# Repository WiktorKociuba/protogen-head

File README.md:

# Protogen head
 <br>
It is a wearable protogen fursuit head that you can make at home! Just follow the readme bellow :3 I made it because I wanted to make a fursuit for a long time and I wanted to challenge my hardware skills as well as learn more about blender.
## Hardware
The PCB for this protogen head contains ESP32-S3-WROOM-1 and is powered by two USB-C ports/one USB-C port and XT-30 connector. You can connect to it:
- Two serialy connected HUB75 LED matrixes
- Two WS2812B LED strips (or any addresable LEDs)
- Two small fans
- One speaker
- One capacitive button <br>

It also has 10 GPIO pins exposed as well as two of each voltage pins. The +5VD net is used to power only LED Matrixes and the +5V powers the rest. ESP32 works on 3V3, so I had to use a LDO to power it. There are also two 74AHCT245PW used to change the logic voltage from 3V3 to 5V, so it can communicate with the peripherals that require 5V. The production files can be found in hardware/protogenHead/jlcpcb/production_files . <br>
 <br>
<br>
<br>
<br>

## 3D Model
You need at least 1700g of filament to print it. I recommend using PETG or something stronger, avoid PLA because it might not be strong enough. This protogen features two pairs of ears with a pair of side panels. It can also accomodate two Waveshare 20117 screens, PCB, two fans and you can additionally make a capacitive touch sensor to detect boops. Just connect a piece of for example aluminum foil via a wire to the designated PCB pin. Remember to calibrate the threshold value by checking how it changes when touched. Everything is mounted using M3 screws, you additionally need heat inserts for the ears.
 <br>

## Software
The source code is mainly in file software/src/main.cpp It has comments, so I will only describe here the functionality. In the future I want to add the ability to control the board over WiFi.
### LED Matrix control
The software uses ESP32-HUB75-MatrixPanel-I2S-DMA library. The pins are setup for the provided PCB so if you want to use your own, just modify it. It comes preloaded with one animation, you have to convert the bitmaps to header files that contain the pixel values. See the example files in software/src on how it looks like. Remember that the arrays have to be the size of your LED number.
### Additional LED control
You can connect two additional programmable LED strips/rings that share the same control pin. Then you just have to change the color to whatever you like in setLEDColor.
### Boop detection
You can add a capacitive sensor to the touch pin. You just have to test what values it gives back and set the threshold accordingly. I use it to play a sound using the FIT0449 speaker. Just provide a SoundData.h with the values of sound exported from Audacity or simmilar program. You can check out the example in software/src.
## How to build (will add more details after I build it)
1) Order the PCB using the gerber files provided in hardware/productionFiles
2) Order all components according to the BoM below
3) Print all the parts provided in 3D Models/print
4) Assemble the PCB and upload software using the opposite port to the ESP32
5) Vacuum form the visor (look at the tutorial provided in section vacuum forming)
6) Glue the magnets to the visor and to the bottom jaw.
7) Fur the base as you wish
8) Screw everything together with M3 screws, remember to embed heat inserts into the ears
9) Attach the visor and power everything with two USB-C cables connected to a powerbank or one USB-C cable on the port opposite to the ESP-32 and one battery connected to the XT30 connector.
### Vacuum forming
In order to vacuum form the visor, check the blender file to see how the vacuum forming rig looks like. Basically you have to use two plywood sheets for top and bottom, the top one should be perforated. Make a box with walls from square timber and connect everything with wood screws. Remember to seal everything with for example caulk or other sealant. You also have to make a hole for your vacuum tube and seal eat. You can also add rails to aid you with alligning the frame, just connect it to the box with for example corner braces. After that make the fram from square timber that will fit the PETG sheet, attach it together with wood screws so that it clamps the PETG sheet. You should also use some sandpaper or something that will create a lot of friction between the petg sheet and the frame, so it doesn't slip out. After that heat up the PETG sheet in oven until it sags, turn on the vacuum and then quickly press the PETG sheet onto the mold. Hold it there for few seconds and then it should be ready to go. Just cut it to shape and then dye it with iDye Poly or something simillar.

## BoM
### PCB
#### PCB Manufacturing

| Component | Qty | Price per item | Price |
| --------- | --- | -------------- | ----- |
| PCB (JLCPCB) | 10 | $0.5 | $5 |
| Stencil (JLCPCB) | 1 | $2.5 | $2.5 |
| Total | | | $7.5 |

#### PCB Components
| Designator | Component | Qty | Price Per Unit | Price |
| ---------- | --------- | --- | -------------- | ----- |
| C10 | [GRM219R61C226ME15L](https://www.tme.eu/pl/details/grm219r61c226me15l/) | 2 | 1.507 PLN | 3.01 PLN |
| C9, C11, C12 | [CL21A106KPFNNNG](https://www.tme.eu/pl/details/cl21a106kpfnnng/) | 10 | 0.333 PLN | 3.33 PLN |
| J1, J2 | [DG301-5.0-2P12](https://www.tme.eu/pl/details/dg301-5.0-2p12/) | 2 | 0.88 PLN | 1.76 PLN |
| C3 | [GRM188R60J106KE47D](https://www.tme.eu/pl/details/grm188r60j106ke47d/) | 10 | 0.145 PLN | 1.45 PLN |
| J8, J9 | [B2B-XH-A](https://www.tme.eu/pl/details/b2b-xh-a/) | 2 | 0.365 PLN | 0.73 PLN |
| C4, C6, C7, C8 | [CL10B104JB8NNNC](https://www.tme.eu/pl/details/cl10b104jb8nnnc/) | 10 | 0.248 PLN | 2.48 PLN |
| R4, R5 | [ERJ3EKF27R0V](https://www.tme.eu/pl/details/erj3ekf27r0v/) | 10 | 0.113 PLN | 1.13 PLN |
| R6, R7, R8, R9 | [ERJ3EKF5101V](https://www.tme.eu/pl/details/erj3ekf5101v/) | 10 | 0.079 PLN | 0.79 PLN |
| J11 | [ZL202-8G](https://www.tme.eu/pl/details/zl202-8g/) | 10 | 0.452 PLN | 4.52 PLN |
| U1 | [T821-1-16-S1](https://www.tme.eu/pl/details/t821-1-16-s1/) | 2 | 4.138 PLN | 8.28 PLN |
| J14 | [67997-410HLF](https://www.tme.eu/pl/details/67997-410hlf/) | 1 | 1.1 PLN | 1.1 PLN |
| R1, R2, R3 | [ERJ3EKF1002V](https://www.tme.eu/pl/details/erj3ekf1002v/) | 10 | 0.036 PLN | 0.36 PLN | 
| J10 | [XT30U-F](https://www.tme.eu/pl/details/xt30u-f/) | 1 | 4.45 PLN | 4.45 PLN |
| J12 | [DS1002-01-1X08V13](https://www.tme.eu/pl/details/ds1002-01-1x08v13/) | 5 | 1.349 PLN | 6.75 PLN |
| U2 | [ESP32S3-WRM1-16R8](https://www.tme.eu/pl/details/esp32s3-wrm1-16r8/) | 1 | 31.48 PLN | 31.48 PLN |
| J4, J5, J6 | [B3B-XH-A](https://www.tme.eu/pl/details/b3b-xh-a/) | 3 | 0.505 PLN | 1.52 PLN |
| U5, U6 | [74AHCT245PW.118](https://www.tme.eu/pl/details/74ahct245pw.118/) | 4 | 1.606 PLN | 6.43 PLN |
| J3, J7 | [USB4105-GF-A](https://www.tme.eu/pl/details/usb4105-gf-a/) | 3 | 3.535 PLN | 10.61 PLN |
| U3 | [AP2112K-3.3TRG1](https://www.tme.eu/pl/details/ap2112k-3.3trg1/) | 2 | 1.173 PLN | 2.35 PLN |
| C1, C2, C5 | [CC0603KRX7R8BB105](https://www.tme.eu/pl/details/cc0603krx7r8bb105/) | 10 | 0.411 PLN | 4.11 PLN |
| SW3, SW4 | [KMR221GLFS](https://www.tme.eu/pl/details/kmr221glfs/) | 3 | 2.401 PLN | 7.20 PLN |
| Pin cover | [NDR-08](https://www.tme.eu/pl/details/ndr-08/) | 10 | 0.574 PLN | 5.74 PLN |
| Pin cover | [NSR-02](https://www.tme.eu/pl/details/nsr-02/) | 20 | 0.24 PLN | 4.79 PLN |
| Total | | | | 114.35 PLN (~$28.12) |

### Other hardware 
| Component | Qty | Price per item | Price |
| --------- | --- | -------------- | ----- |
| [Waveshare 20117](https://kamami.pl/matrycowe/587574-rgb-matrix-p3-64x32-wyswietlacz-matrycowy-led-rgb-64x32-5906623465668.html) | 2 | 125.50 PLN | 251 PLN |
| [FIT0449](https://botland.com.pl/gravity-moduly-dzwiekowe/5501-dfrobot-gravity-glosnik-z-interfejsem-cyfrowym-6959420909575.html) | 1 | 26.90 PLN | 26.90 PLN
| [WS2812B](https://nettigo.pl/products/tasma-led-rgb-ws2812b-5v-bialy-podklad-60-m-ip67-wodoodporna) | 1 | 31 PLN | 31 PLN |
| [Sunon 1197317](https://kamami.pl/wentylatory/1197317-sunon-ee40100s2-1000u-999-5902186301221.html) | 2 | 10.20 PLN | 20.40 PLN |
| Total | | | 316.96 PLN (~$77.97)

### Vacuum forming
| Component | Qty | Price per item | Price |
| --------- | --- | -------------- | ----- |
| [50x50cm plywood](https://www.castorama.pl/departments/sklejka-brzozowa-wodoodporna-fosztt-6-mm-50-x-50-cm-1-szt/5908110070805_CAPL.prd) | 2 | 25 PLN | 50 PLN |
| [Square timber 19x60x1000mm](https://www.castorama.pl/kantowka-strugana-drewniana-floorpol-19-x-60-x-1000-mm/5907508714062_CAPL.prd) | 2 | 13.98 PLN | 27.96 PLN |
| [Square timber 10x40x1000mm](https://www.castorama.pl/kantowka-strugana-ostre-krawedzie-sosna-10x40x1000-mm/5063022667830_CAPL.prd) | 4 | 10.88 PLN | 43.52 PLN|
| [Square timber 10x10x1000mm](https://www.castorama.pl/kantowka-strugana-ostre-krawedzie-sosna-10x10x1000-mm/5063022667250_CAPL.prd) | 1 | 6.58 PLN | 6.58 PLN |
| [Corner brace](https://www.castorama.pl/katownik-stalowy-do-laczenia-elementow-z-przetloczeniem-25-x-25-x-15-mm-ocynk-bialy/5907484582167_CAPL.prd) | 4 | 2.98 PLN | 11.92 PLN |
| [Wood screw 6x100mm 10pcs](https://www.castorama.pl/wkrety-torx-diall-do-drewna-twardego-6-x-100-mm-10-szt-/5906675097350_CAPL.prd) | 1 | 13.98 PLN | 13.98 PLN |
| [Caulk](https://www.castorama.pl/silikon-uniwersalny-300-ml-bezbarwny/5059340043647_CAPL.prd) | 1 | 11 PLN | 11 PLN |
| [PETG Sheet 50x50cm 3mm](https://fabermedia.pl/plyty-z-tworzyw-sztucznych/plyty-pet/plyta-pet-bezbarwna-pet-g-3mm#/grubo%C5%9B%C4%87-3mm) | 2 | 52.54 PLN | 105.08 PLN |
| [iDye Poly Black](https://allegro.pl/produkt/jacquard-idye-poly-0-49oz-black-czarny-barwnik-do-tkanin-syntetycznych-a346e01e-34aa-4d9d-9f90-61f1dbddb3e5?offerId=19117603692&utm_source=google&utm_medium=product-carousel&utm_campaign=product-listing&utm_content=%2Flisting%3Fstring%3Didye%2520poly) | 1 | 35.68 PLN | 35.68 PLN | 
| Total | | | 305.72 PLN (~$74.83) |

### Other
| Component | Qty | Price per item | Price |
| --------- | --- | -------------- | ----- |
| [Screws M3 x 10mm 20pcs](https://www.castorama.pl/sruby-metryczne-z-lbem-cylindrycznym-ocynkowane-m3-x-10-mm-20-szt-/4001221784546_CAPL.prd) | 1 | 8.48 PLN | 8.48 PLN |
| [Screws M3 x 20mm 20pcs](https://www.castorama.pl/sruby-metryczne-z-lbem-cylindrycznym-ocynkowane-m3-x-20-mm-20-szt-/4001221784317_CAPL.prd) | 1 | 8.18 PLN | 8.18 PLN |
| [M3 Heat-set inserts](https://www.tme.eu/pl/details/b3_bn1045/wkladki-gwintowane/bossard/1386204/) | 10 | 0.511 PLN | 5.11 PLN |
| [Creality CR-PETG black](https://botland.com.pl/filamenty-petg/23007-filament-creality-cr-petg-175mm-1kg-black-6971636405344.html) | 2 | 49 PLN | 98 PLN |
| [Black fur](https://efutro.com.pl/product-pol-372-Fox-PREMIUM-365-czarny-Black-Frost-sztuczne-futro-niezwykle-puszyste-z-wlosem-o-dlugosci-do-60-mm.html) | 1 lm | 170.10 PLN | 170.10 PLN |
| [Purple fur](https://efutro.com.pl/product-pol-608-Fox-Fioletowy-2074-sztuczne-futro-niezwykle-puszyste-z-wlosem-o-dlugosci-do-60-mm.html?rec=104002103) | 0.5 lm | 86.10 PLN | 86.10 PLN | 
| [Magnets 10x4mm](https://kamami.pl/magnesy-trwale/1186637-mno-100x040-10-szt-magnes-neodymowy--5906623484065.html) | 20 | 2.793 PLN | 55.86 PLN |
| [JST-XH Connectors](https://allegro.pl/oferta/zlacza-jst-xh-raster-2-54-mm-2-3-4-pin-konektory-styki-zestaw-250szt-11401212667?bi_s=ads&bi_m=productlisting:desktop:query&bi_c=ZjEzM2Y1NmQtOWU0OS00YWQ0LWJkZDMtOTZmZWJlZDlmODBiAA&bi_t=ape&referrer=proxy&emission_unit_id=5d068c31-d72c-4411-b63b-5e8a12a4023c) | 1 | 14.63 PLN | 14.63 PLN |
| [Crimping tool](https://allegro.pl/oferta/zaciskarka-reczna-praska-do-konektorow-zlacz-nieizolowanych-kabli-sn-48b-14377876311?bi_s=ads&bi_m=showitem:desktop:department:active&bi_c=ZWMwNjY5YjEtOTRmZi00MWMxLWEwNTktZTg2OGJlOWU4MzIzAA&bi_t=ape&referrer=proxy&emission_unit_id=39021d95-b789-4270-b3f9-fa66eabc7824) | 1 | 42.75 PLN | 42.75 PLN |
| [Solder Paste](https://kamami.pl/pasty-lutownicze/584387-artagt-023-pasta-lutownicza-easy-print-14-ml-strzykawka-5901764329244.html) | 1 | 19.26 PLN | 19.26 PLN |
| [Heat bed for soldering](https://allegro.pl/produkt/stol-grzewczy-do-plytki-lutowniczej-pcb-smd-d6cac185-a49f-413a-99a0-2827dde03938?offerId=17143392881) | 1 | 92.66 PLN | 92.66 PLN |
| Total | | | 601.13 PLN (~$147.14) |

The total price for all of the components is ~$335.56. This price excludes shipping costs. Some of the components have also MoQ that is higher than required number of them, so in that case I put the MoQ value. I also included a little surplus of small smd components as they are easy to lose and cost very little. I also included one extra PETG sheet as it is very likely to fail the first attempt.

### Shipping
| Supplier | Cost |
| -------- | ---- |
| JLCPCB | $14.77 |
| tme.eu | 15.90 PLN |
| kamami | 8.90 PLN |
| nettigo | 17.50 PLN |
| fabermedia | 15 PLN |
| Allegro | 35 PLN | 
| Botland | 15 PLN |
| efutro | 15 PLN |
| Total | $14.77 + 122.3 PLN (~$44.7)

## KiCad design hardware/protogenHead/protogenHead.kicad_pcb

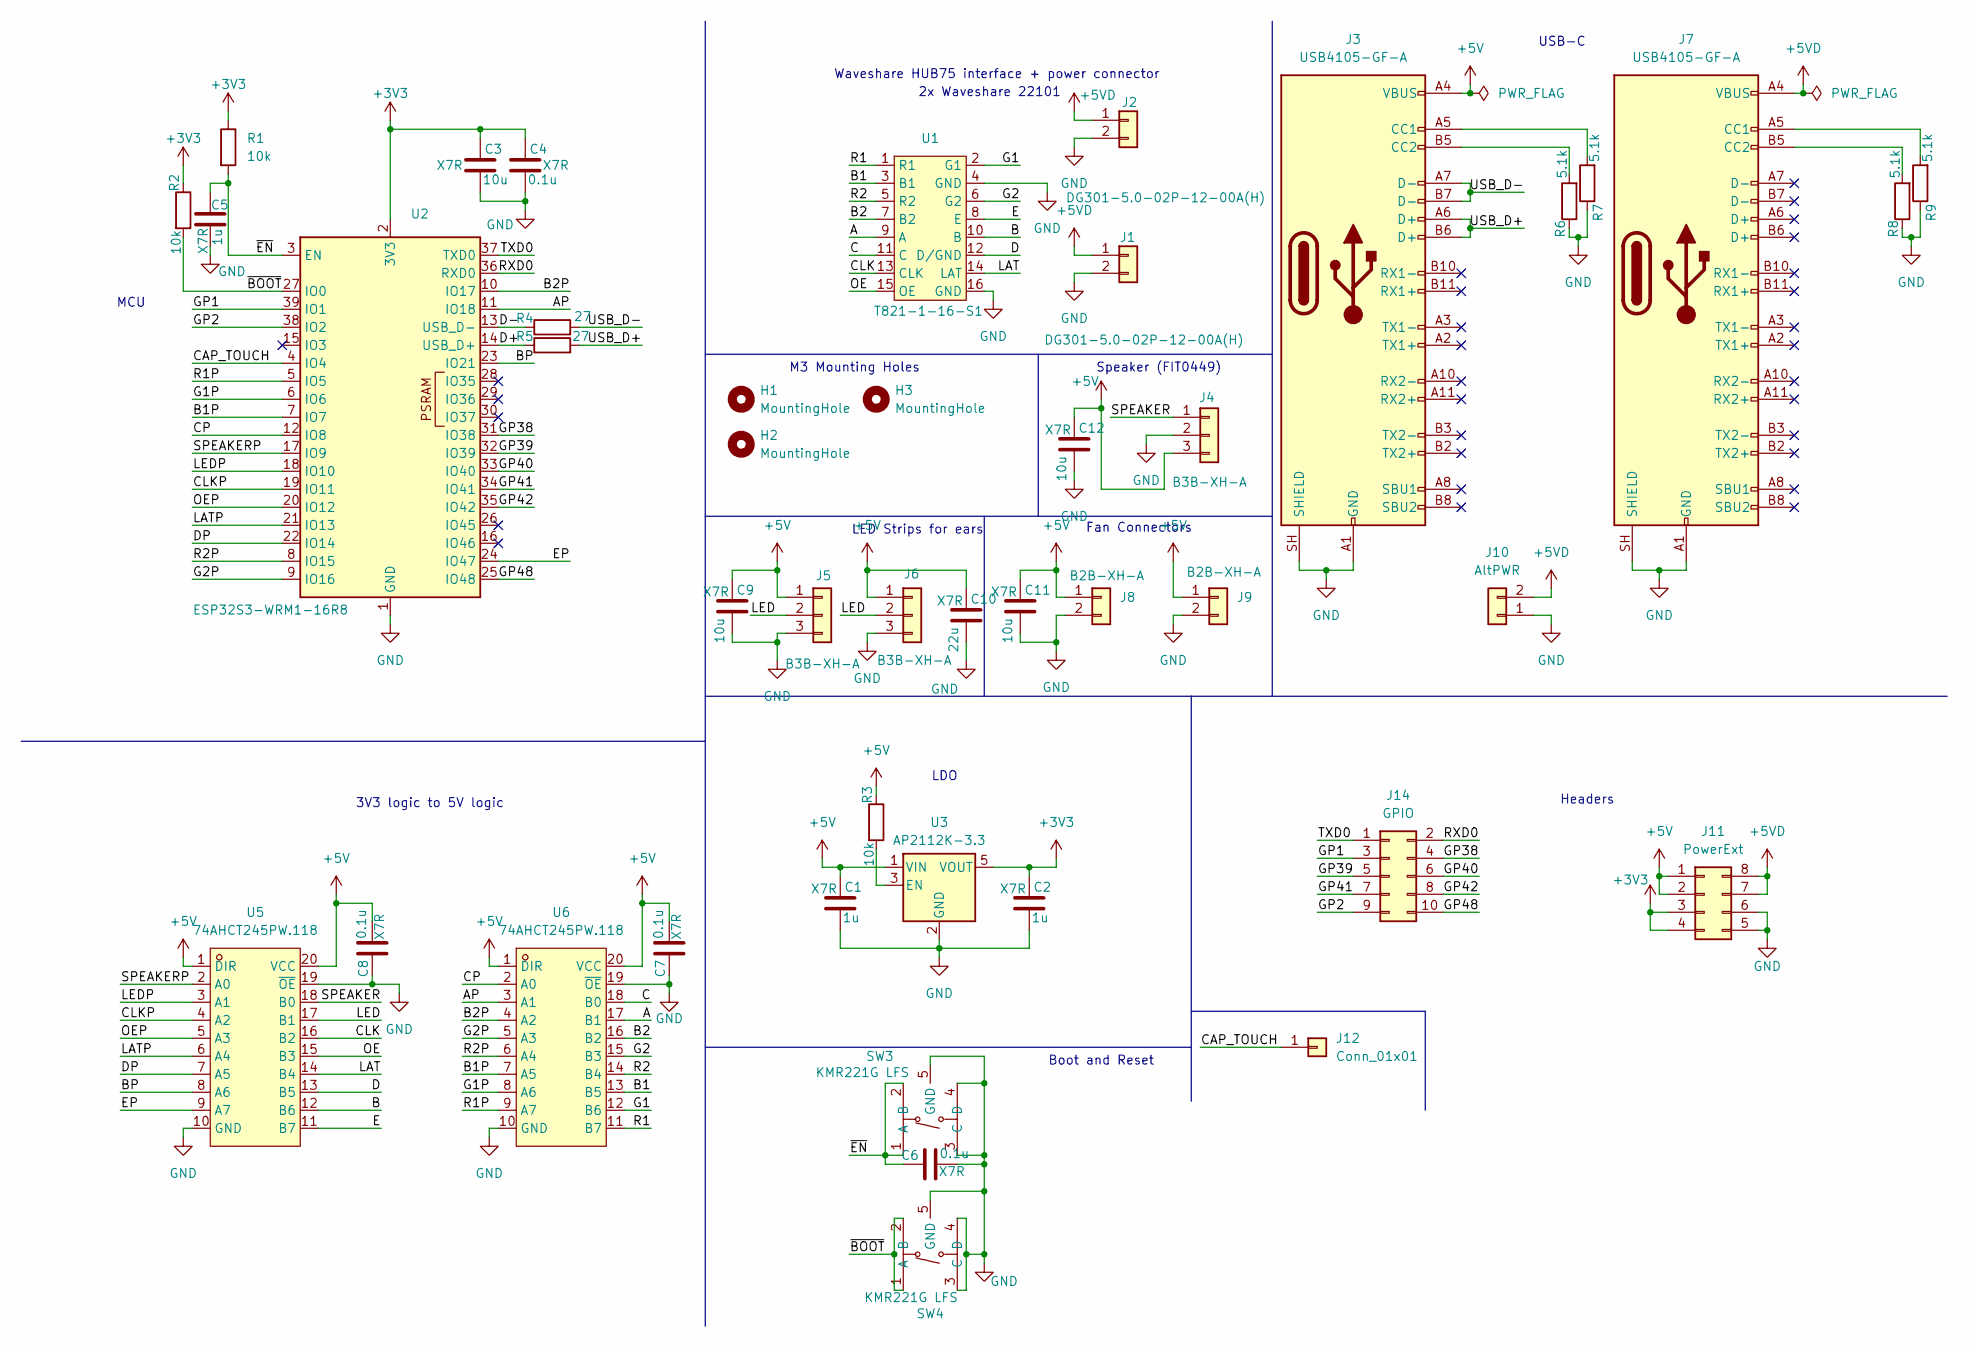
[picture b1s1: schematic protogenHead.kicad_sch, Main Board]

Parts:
C1, C2, C5: 1u; C_0603_1608Metric
C3: 10u; C_0603_1608Metric
C4, C6, C7, C8: 0.1u; C_0603_1608Metric
C9, C11, C12: 10u; C_0805_2012Metric
C10: 22u; C_0805_2012Metric
H1, H2, H3: MountingHole; MountingHole_3.2mm_M3
J1, J2: DG301-5.0-02P-12-00A(H); DG3015002P1200AH
J3, J7: USB4105-GF-A; USB_C_Receptacle_GCT_USB4105-xx-A_16P_TopMnt_Horizontal
J4, J5, J6: B3B-XH-A; JST_XH_B3B-XH-A_1x03_P2.50mm_Vertical
J8, J9: B2B-XH-A; JST_XH_B2B-XH-A_1x02_P2.50mm_Vertical
J10: AltPWR; AMASS_XT30U-F_1x02_P5.0mm_Vertical
J11: PowerExt; PinHeader_2x04_P2.54mm_Vertical
J12: Conn_01x01; PinSocket_1x01_P2.54mm_Vertical
J14: GPIO; PinHeader_2x05_P2.54mm_Vertical
R1, R2, R3: 10k; R_0603_1608Metric
R4, R5: 27; R_0603_1608Metric
R6, R7, R8, R9: 5.1k; R_0603_1608Metric
SW3, SW4: KMR221G LFS; KMR221GLFS; MPN TS-1187A-B-A-B; LCSC Part C318884
U1: T821-1-16-S1; IDC-Header_2x08_P2.54mm_Vertical
U2: ESP32S3-WRM1-16R8; ESP32-S3-WROOM-1
U3: AP2112K-3.3; SOT-23-5
U5, U6: 74AHCT245PW.118; TSSOP-20_L6.5-W4.4-P0.65-LS6.4-BL; MPN 74AHCT245PW; LCSC Part C54815895

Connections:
+3V3: C2.1, C3.1, C4.1, J11.3, J11.4, R1.1, R2.1, U2.2 (3V3), U3.5 (VOUT)
+5V: C1.1, C7.2, C8.2, C9.1, C10.1, C11.1, C12.1, J3.A4 (VBUS), J3.A9 (VBUS), J3.B4 (VBUS), J3.B9 (VBUS), J4.3, J5.1, J6.1, J8.1, J9.1, J11.1, J11.2, R3.1, U3.1 (VIN), U5.1 (DIR), U5.20 (VCC), U6.1 (DIR), U6.20 (VCC)
+5VD: J1.1, J2.1, J7.A4 (VBUS), J7.A9 (VBUS), J7.B4 (VBUS), J7.B9 (VBUS), J10.2, J11.7, J11.8
/A: U1.9 (A), U6.17 (B1)
/AP: U2.11 (IO18), U6.3 (A1)
/B: U1.10 (B), U5.12 (B6)
/B1: U1.3 (B1), U6.13 (B5)
/B1P: U2.7 (IO7), U6.7 (A5)
/B2: U1.7 (B2), U6.16 (B2)
/B2P: U2.10 (IO17), U6.4 (A2)
/BP: U2.23 (IO21), U5.8 (A6)
/C: U1.11 (C), U6.18 (B0)
/CAP_TOUCH: J12.1 (Pin_1_1), U2.4 (IO4)
/CLK: U1.13 (CLK), U5.16 (B2)
/CLKP: U2.19 (IO11), U5.4 (A2)
/CP: U2.12 (IO8), U6.2 (A0)
/D: U1.12 (D/GND), U5.13 (B5)
/D+: R5.1, U2.14 (USB_D+)
/D-: R4.1, U2.13 (USB_D-)
/DP: U2.22 (IO14), U5.7 (A5)
/E: U1.8 (E), U5.11 (B7)
/EP: U2.24 (IO47), U5.9 (A7)
/G1: U1.2 (G1), U6.12 (B6)
/G1P: U2.6 (IO6), U6.8 (A6)
/G2: U1.6 (G2), U6.15 (B3)
/G2P: U2.9 (IO16), U6.5 (A3)
/GP1: J14.3, U2.39 (IO1)
/GP2: J14.9, U2.38 (IO2)
/GP38: J14.4, U2.31 (IO38)
/GP39: J14.5, U2.32 (IO39)
/GP40: J14.6, U2.33 (IO40)
/GP41: J14.7, U2.34 (IO41)
/GP42: J14.8, U2.35 (IO42)
/GP48: J14.10, U2.25 (IO48)
/LAT: U1.14 (LAT), U5.14 (B4)
/LATP: U2.21 (IO13), U5.6 (A4)
/LED: J5.2, J6.2, U5.17 (B1)
/LEDP: U2.18 (IO10), U5.3 (A1)
/OE: U1.15 (OE), U5.15 (B3)
/OEP: U2.20 (IO12), U5.5 (A3)
/R1: U1.1 (R1), U6.11 (B7)
/R1P: U2.5 (IO5), U6.9 (A7)
/R2: U1.5 (R2), U6.14 (B4)
/R2P: U2.8 (IO15), U6.6 (A4)
/RXD0: J14.2, U2.36 (RXD0)
/SPEAKER: J4.1, U5.18 (B0)
/SPEAKERP: U2.17 (IO9), U5.2 (A0)
/TXD0: J14.1, U2.37 (TXD0)
/USB_D+: J3.A6 (D+), J3.B6 (D+), R5.2
/USB_D-: J3.A7 (D-), J3.B7 (D-), R4.2
/~BOOT: R2.2, SW4.1 (A), SW4.2 (B), U2.27 (IO0)
/~EN: C5.1, C6.1, R1.2, SW3.1 (A), SW3.2 (B), U2.3 (EN)
GND: C1.2, C2.2, C3.2, C4.2, C5.2, C6.2, C7.1, C8.1, C9.2, C10.2, C11.2, C12.2, J1.2, J2.2, J3.A1 (GND), J3.A12 (GND), J3.B1 (GND), J3.B12 (GND), J3.SH (SHIELD), J4.2, J5.3, J6.3, J7.A1 (GND), J7.A12 (GND), J7.B1 (GND), J7.B12 (GND), J7.SH (SHIELD), J8.2, J9.2, J10.1, J11.5, J11.6, R6.1, R7.1, R8.1, R9.1, SW3.3 (C), SW3.4 (D), SW3.5 (GND), SW4.3 (C), SW4.4 (D), SW4.5 (GND), U1.4 (GND), U1.16 (GND), U2.1 (GND), U2.40 (GND), U2.41 (GND), U3.2 (GND), U5.10 (GND), U5.19 (~OE), U6.10 (GND), U6.19 (~OE)
unnamed: J3.A5 (CC1), R7.2
unnamed: J3.B5 (CC2), R6.2
unnamed: J7.A5 (CC1), R9.2
unnamed: J7.B5 (CC2), R8.2
unnamed: R3.2, U3.3 (EN)

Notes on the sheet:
3V3 logic to 5V logic
Boot and Reset
M3 Mounting Holes
USB-C
Fan Connectors
Speaker (FIT0449)
LDO
Waveshare HUB75 interface + power connector
LED Strips for ears
2x Waveshare 22101
Headers
MCU

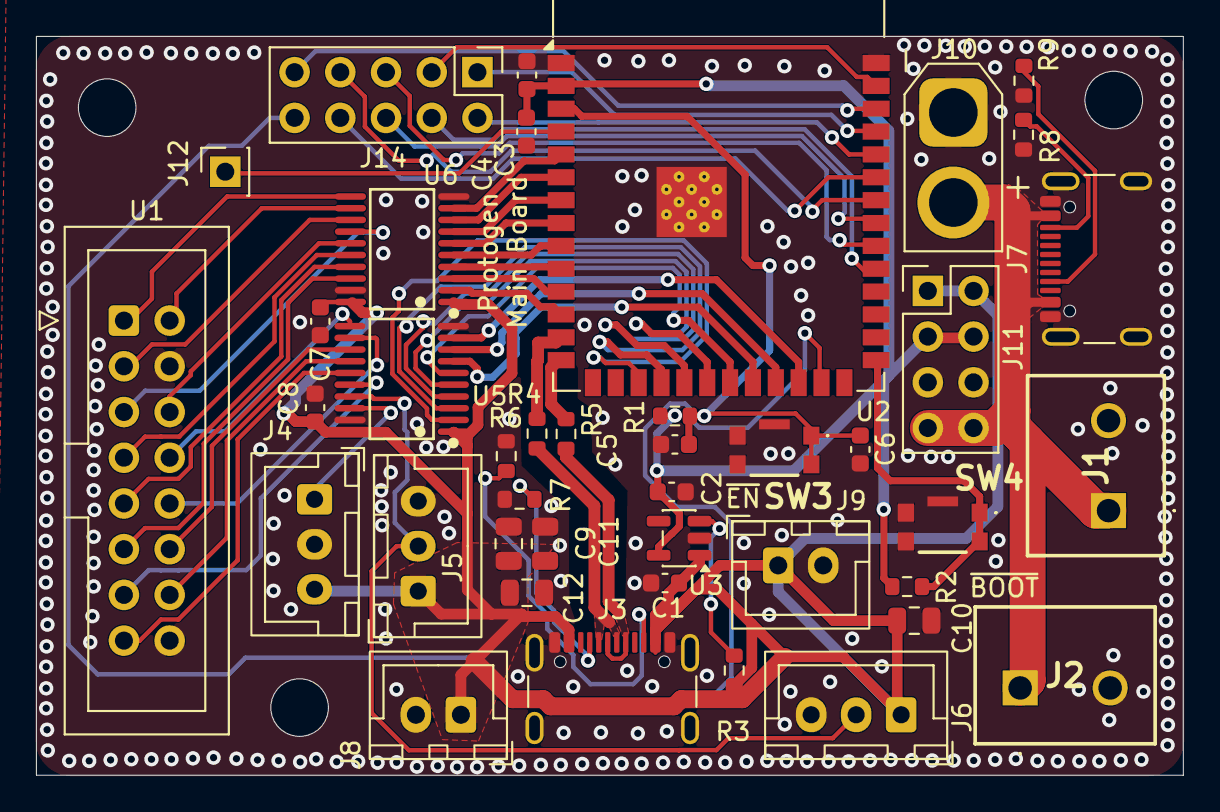
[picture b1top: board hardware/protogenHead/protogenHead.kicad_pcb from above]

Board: 2 copper layers, 63.7 x 41.0 mm, 44 parts (0 on the bottom side), 58 nets.

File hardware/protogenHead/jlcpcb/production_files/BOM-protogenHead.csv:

Comment,Designator,Footprint,LCSC,Quantity
0.1u,"C4,C6,C7,C8",C_0603_1608Metric,C45000,4
10k,"R1,R2,R3",R_0603_1608Metric,C25804,3
10u,C3,C_0603_1608Metric,C19702,1
1u,"C1,C2,C5",C_0603_1608Metric,C15849,3
5.1k,"R6,R7,R8,R9",R_0603_1608Metric,C23186,4
74AHCT245PW.118,"U5,U6",TSSOP-20_L6.5-W4.4-P0.65-LS6.4-BL,C54815895,2
AP2112K-3.3,U3,SOT-23-5,C23380830,1
AltPWR,J10,AMASS_XT30U-F_1x02_P5.0mm_Vertical,C99102,1
Conn_01x01,J12,PinSocket_1x01_P2.54mm_Vertical,C49569624,1
ESP32S3-WRM1-16R8,U2,ESP32-S3-WROOM-1,C2913202,1
GPIO,J14,PinHeader_2x05_P2.54mm_Vertical,C5383106,1
KMR221G LFS,"SW3,SW4",KMR221GLFS,C318884,2
PowerExt,J11,PinHeader_2x04_P2.54mm_Vertical,C5383105,1
T821-1-16-S1,U1,IDC-Header_2x08_P2.54mm_Vertical,C2884532,1
DG301-5.0-02P-12-00A(H),J1,DG3015002P1200AH,,1
27,R4,R_0603_1608Metric,,1
27,R5,R_0603_1608Metric,,1
B2B-XH-A,J9,JST_XH_B2B-XH-A_1x02_P2.50mm_Vertical,,1
B2B-XH-A,J8,JST_XH_B2B-XH-A_1x02_P2.50mm_Vertical,,1
USB4105-GF-A,J7,USB_C_Receptacle_GCT_USB4105-xx-A_16P_TopMnt_Horizontal,,1
B3B-XH-A,J6,JST_XH_B3B-XH-A_1x03_P2.50mm_Vertical,,1
B3B-XH-A,J5,JST_XH_B3B-XH-A_1x03_P2.50mm_Vertical,,1
B3B-XH-A,J4,JST_XH_B3B-XH-A_1x03_P2.50mm_Vertical,,1
USB4105-GF-A,J3,USB_C_Receptacle_GCT_USB4105-xx-A_16P_TopMnt_Horizontal,,1
DG301-5.0-02P-12-00A(H),J2,DG3015002P1200AH,,1
10u,C12,C_0805_2012Metric,,1
10u,C11,C_0805_2012Metric,,1
22u,C10,C_0805_2012Metric,,1
10u,C9,C_0805_2012Metric,,1

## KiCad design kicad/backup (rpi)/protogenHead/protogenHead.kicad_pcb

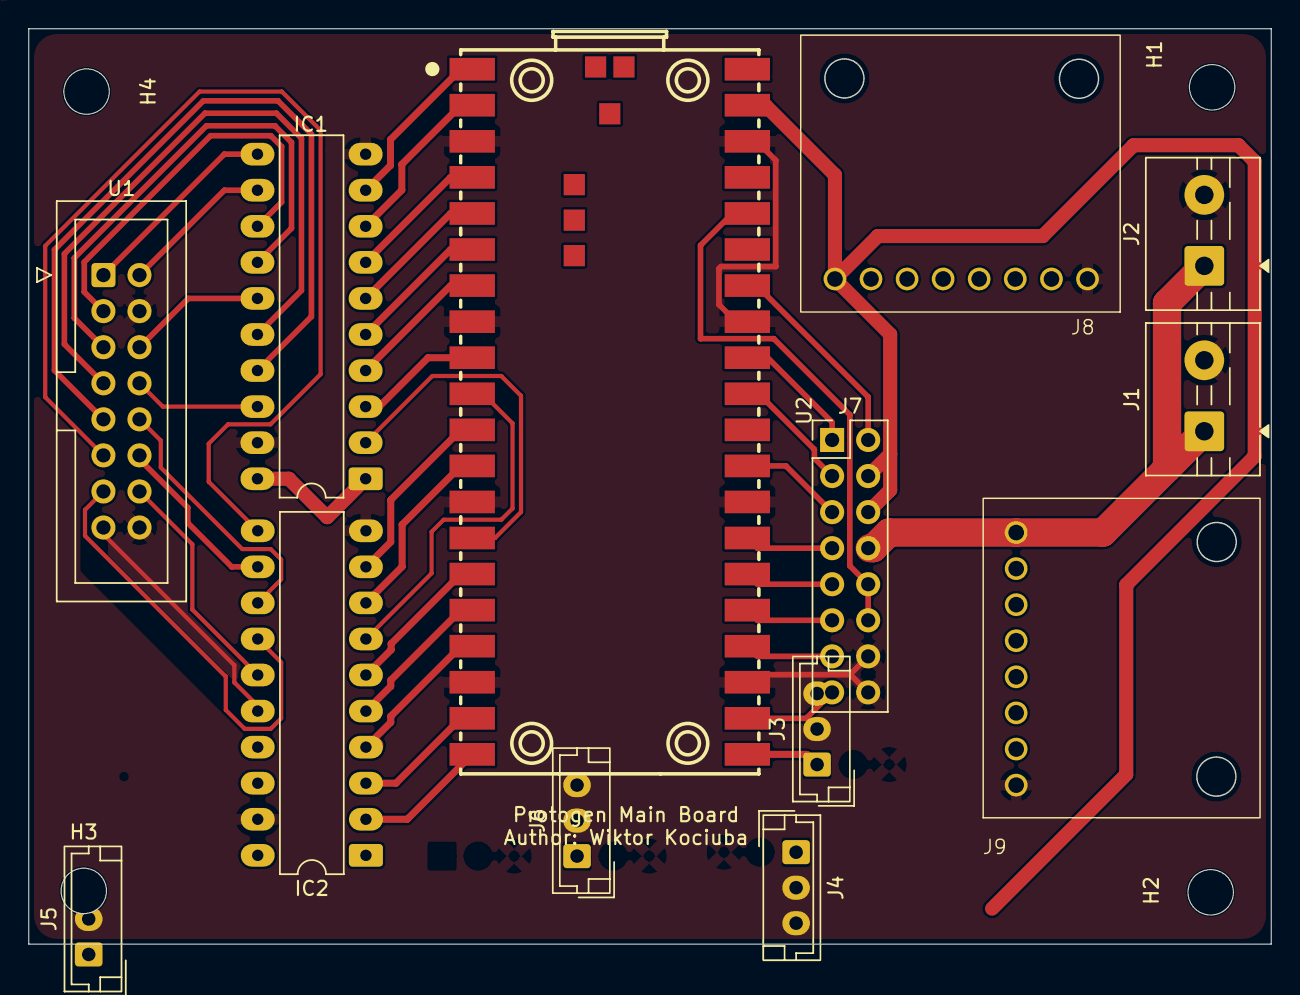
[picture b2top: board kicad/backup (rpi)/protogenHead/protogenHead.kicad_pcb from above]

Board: 2 copper layers, 87.5 x 64.5 mm, 17 parts (0 on the bottom side), 46 nets.

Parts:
H1, H2, H3, H4: MountingHole; MountingHole_3.2mm_M3
IC1, IC2: 74HCT245; DIP-20_W7.62mm_LongPads
J1: Power1; TerminalBlock_MaiXu_MX126-5.0-02P_1x02_P5.00mm
J2: Power2; TerminalBlock_MaiXu_MX126-5.0-02P_1x02_P5.00mm
J3: MotionSensor; JST_EH_B3B-EH-A_1x03_P2.50mm_Vertical
J4: FIT0449; JST_EH_B3B-EH-A_1x03_P2.50mm_Vertical
J5, J6: WS2812B; JST_EH_B3B-EH-A_1x03_P2.50mm_Vertical
J7: GPIO Header; PinHeader_2x08_P2.54mm_Vertical
J8, J9: PiHut 106575; PiHut USB-C
U1: HUB75; IDC-Header_2x08_P2.54mm_Vertical
U2: RASPBERRY PI PICO 2W; Pi Pico 2W

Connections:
+3V3: J3.2, J7.10, J7.12, U2.36 (3V3(OUT))
+5V: IC1.1 (DIR), IC1.20 (VCC), IC2.1 (DIR), IC2.20 (VCC), J4.2, J5.1, J6.1, J7.4, J7.6, J8.A4 (VBUS), U2.39 (VSYS)
+5VD: J1.1, J2.1, J7.8, J9.A4 (VBUS)
/A: IC1.17 (B2), U1.9 (A)
/AP: IC1.3 (A2), U2.9 (GP6_SPI0SCK_I2C1SDA)
/B: IC2.13 (B6), U1.10 (B)
/B1: IC1.13 (B6), U1.3 (B1)
/B1P: IC1.7 (A6), U2.4 (GP2_SPI0SCK_I2C1SDA)
/B2: IC1.16 (B3), U1.7 (B2)
/B2P: IC1.4 (A3), U2.7 (GP5_SPI0CSn_I2C0SCL_UART1RX)
/BP: IC2.7 (A6), U2.10 (GP7_SPI0TX_I2C1SCL)
/C: IC2.11 (B8), U1.11 (C)
/CLK: IC2.14 (B5), U1.13 (CLK)
/CLKP: IC2.6 (A5), U2.15 (GP11_SPI1TX_I2C1SCL)
/CP: IC2.9 (A8), U2.11 (GP8_SPI1RX_I2C0SDA_UART1TX)
/D: IC2.12 (B7), U1.12 (D/GND)
/DP: IC2.8 (A7), U2.12 (GP9_SPI1CSn_I2C0SCL_UART1RX)
/E: IC1.18 (B1), U1.8 (E)
/EP: IC1.2 (A1), U2.14 (GP10_SPI1SCK_I2C1SDA)
/G1: IC1.12 (B7), U1.2 (G1)
/G1P: IC1.8 (A7), U2.2 (GP1_SPI0CSn_I2C0SCL_UART0RX)
/G2: IC1.15 (B4), U1.6 (G2)
/G2P: IC1.5 (A4), U2.6 (GP4_SPI0RX_I2C0SDA_UART1TX)
/GP17: J7.15, U2.22 (GP17_SPI0CSn_UART0TX)
/GP18: J7.13, U2.24 (GP18_SPI0SCK_I2C1SDA)
/GP19: J7.11, U2.25 (GP19_SPI0TX_I2C1SCL)
/GP20: J7.9, U2.26 (GP20_I2C0SDA)
/GP21: J7.7, U2.27 (GP21_I2C0SCL)
/GP22: J7.5, U2.29 (GP22)
/GP26: J7.3, U2.31 (GP26_ADC0_I2C1SDA)
/GP27: J7.1, U2.32 (GP27_ADC1_I2C1SCL)
/GP28: J7.2, U2.34 (GP28_ADC2)
/LAT: IC2.15 (B4), U1.14 (LAT)
/LATP: IC2.5 (A4), U2.16 (GP12_SPI1RX_I2C0SDA_UART0TX)
/LED: IC2.17 (B2), J5.2, J6.2
/LEDP: IC2.3 (A2), U2.19 (GP14_SPI1SCK_I2C1SDA)
/MOTION: J3.1, U2.21 (GP16_SPI0RX_UART0RX)
/OE: IC2.16 (B3), U1.15 (OE)
/OEP: IC2.4 (A3), U2.17 (GP13_SPI1CSn_I2C0SCL_UART0RX)
/R1: IC1.11 (B8), U1.1 (R1)
/R1P: IC1.9 (A8), U2.1 (GP0_SPI0RX_I2C0SDA_UART0TX)
/R2: IC1.14 (B5), U1.5 (R2)
/R2P: IC1.6 (A5), U2.5 (GP3_SPI0TX_I2C1SCL)
/SPEAKER: IC2.18 (B1), J4.1
/SPEAKERP: IC2.2 (A1), U2.20 (GP15_SPI1TX_I2C1SCL)
GND: IC1.10 (GND), IC1.19 (~OE), IC2.10 (GND), IC2.19 (~OE), J1.2, J2.2, J3.3, J4.3, J5.3, J6.3, J7.14, J7.16, J8.A1 (GND), J9.A1 (GND), U1.4 (GND), U1.16 (GND), U2.3 (GND), U2.8 (GND), U2.13 (GND), U2.18 (GND), U2.23 (GND), U2.28 (GND), U2.33 (GND_AGND), U2.38 (GND)
